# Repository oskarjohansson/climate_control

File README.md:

# Boot Climate Control
> Created by Benjamin Lundgren & Oskar Johansson

Based on [Ski boots hearing system](https://hackaday.io/project/163132-ski-boots-heating-system). 

## Goals 
> The goal of the Boot Climate Control (BCC)
```
- Never ever freeze in the boots
- Warm for ~8h
```

## Directories 
```
climate_control
├── document        # Generic document folder
│   ├── datasheet   # Datasheet for hardware components  
├── hardware        
│   ├── cad         # 3D models
│   │   └── stl     # 3D print files
│   ├── pcb         # Schematic, layout and production files
│   │   └── gerber  # Production files
│   │   └── library # Library for project
├── img             
└── software        # Firmware files
```

## Usage
> Description about how to use the BCC 

## License
> This template is created with MIT license.
>
> ](http://badges.mit-license.org)

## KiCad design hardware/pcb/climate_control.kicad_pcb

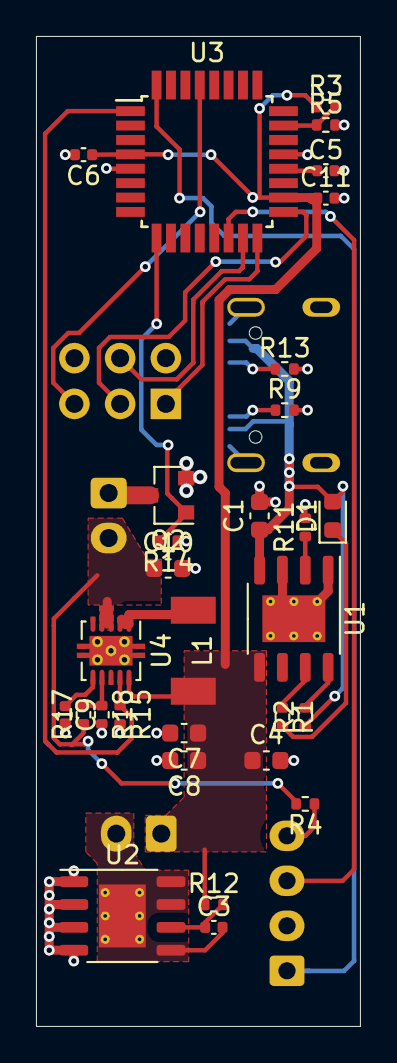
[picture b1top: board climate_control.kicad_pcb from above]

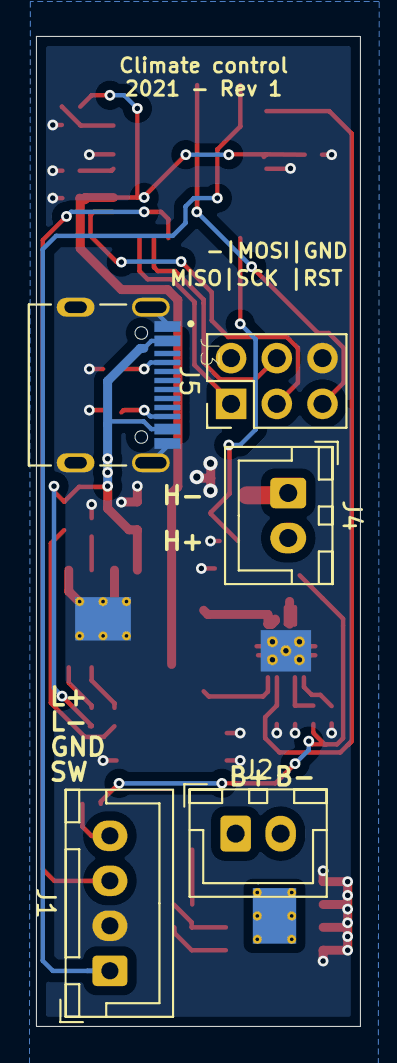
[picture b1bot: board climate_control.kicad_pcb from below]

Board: 2 copper layers, 18.0 x 55.0 mm, 35 parts (5 on the bottom side), 27 nets.

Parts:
C1, C4, C7, C8, C10: 10uF; C_0603_1608Metric
C3, C6, C11: 100nF; C_0402_1005Metric
C5: 1uF; C_0402_1005Metric
C9: 18nF; C_0402_1005Metric
D1: CHRG; D_0603_1608Metric
J1: Switch; JST_XH_B4B-XH-A_1x04_P2.50mm_Vertical
J2: BatteryIn; JST_XH_B2B-XH-A_1x02_P2.50mm_Vertical
J3: USB_C; HRO_TYPE-C-31-M-12
J4: HeatElement; JST_XH_B2B-XH-A_1x02_P2.50mm_Vertical
J5: ICSP; PinHeader_2x03_P2.54mm_Vertical
L1: 1uH; Inductor_0530
Q2: NTR3C21NZ; SOT-23
R1, R4: x; R_0402_1005Metric
R2, R14: 10k; R_0402_1005Metric
R3, R15: 100k; R_0402_1005Metric
R5: 30k; R_0402_1005Metric
R9, R13: 5.1k; R_0402_1005Metric
R11: 2.4k; R_0402_1005Metric
R12: 100R; R_0402_1005Metric
R17, R18: R_Small; R_0402_1005Metric
U1: TP4056; SOP8-EPAD
U2: XB8089A; SOP8-EPAD
U3: ATmega328PB-AU; TQFP-32_7x7mm_P0.8mm
U4: TPS61230DRC; Texas_S-PVSON-N10_ThermalVias

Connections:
+5V: C1.1, D1.2, J3.A4B9, J3.B4A9, R2.1, U1.4
+BATT: C4.1, C6.1, C7.1, C8.1, C11.1, J2.1, L1.1, R3.1, R12.1, U1.5, U3.4, U3.18, U4.10
+VSW: C10.1, J4.2, R4.2, R17.1, U4.3, U4.4
-BATT: C3.2, J2.2, U2.5, U2.7, U2.8, U2.9
BAT: R3.2, R5.1, U3.23
BOOST_EN: R15.1, U3.1, U4.9
GND: C1.2, C4.2, C5.2, C6.2, C7.2, C8.2, C9.2, C10.2, C11.2, J1.2, J3.A1B12, J3.B1A12, J3.S1, J5.6, Q2.2, R5.2, R9.2, R11.2, R13.2, R14.1, R15.2, R18.2, U1.1, U1.3, U1.9, U2.1, U2.2, U2.3, U2.4, U3.5, U3.21, U4.11
HEATER_PWM: Q2.1, R14.2, U3.9
LED: J1.3, U3.14
MISO: J5.1, U3.16
MOSI: J5.4, U3.15
unnamed: C3.1, R12.2, U2.6
unnamed: C5.1, U3.20
unnamed: C9.1, U4.6
unnamed: D1.1, R1.2
unnamed: J1.4, R4.1
unnamed: J3.A5, R13.1
unnamed: J3.B5, R9.1
unnamed: J4.1, Q2.3
unnamed: L1.2, U4.1, U4.2
unnamed: R1.1, U1.7
unnamed: R2.2, U1.8
unnamed: R11.1, U1.2
unnamed: R17.2, R18.1, U4.7
SCK: J5.3, U3.17
SWITCH: J1.1, U3.32
~RST: J5.5, U3.29

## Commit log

2021-02-16 Added components to schematic and library
    Added Battery protection
    Added Boost charger
    Added USB Connector
    Added Boost module
2021-02-16 Added link to hackaday post
2021-02-16 Correct title on battery charger.
    Wrote boost before, when it is a buck charger. Now corrected.
2021-02-17 Added image of Arduino Pro Mini
2021-02-17 Added datasheet for BMS
2021-02-17 Added MCU and better control.
    MCU with all connection is added.
    Output to heater now has a mosfet to PWM to.
    LED Switch has a connection with mosfet to control LED.
    LED Switch has a LP filter for debounce purpose.
2021-02-18 All components added to schematic and pcb.
    Footprints for all parts is done and only routing is left.
2021-02-18 Removed resistor on TP4056.
    Updated on PCB the routing.
2021-02-18 First routing complete.
    The first routing is done, now it must be improved!
2021-02-18 Added comments on LED/Switch circuitry
2021-02-20 Removed unnececary components
2021-02-20 Second routing process done
2021-02-20 Routing complete and added some silkscreen.
2021-02-22 Added datasheet for all components.
    Added datasheet for all components except passives and connectors.
2021-02-22 Added battery divider to MCU.
    A voltage divider from the battery is now connected to the MCU.
    The divider is designed to work with the internal voltage reference (1V1).
    With the resistor values, a battery voltage of 5 V will be 1.15 at MCU.
2021-02-23 Removed crystal.
    The ATMega does not need an external crystal. Now removed.
2021-02-23 Export .stp from PCB.
2021-02-25 Final first revision ordered.
2021-03-11 More preparations in code. (SOC)
2021-03-11 Createt Platform-IO project + structured files
2021-03-16 Changed platformIo settings
    Upload settings for using atmel ice in ubuntu.
    Board frequency and fuses to get correct timing.
2021-03-16 Software verification
    Tested
    - enabling of boost converter
    - toggling led
    - reading button
    - debouncing and click pattern detection
2021-04-12 Fixed sleep and changing power level. Still too high sleep current.
2021-04-13 Fixed sleeping issue and led indication for heater
2021-04-14 Added SOC led blinks.
    The LED will now blink according to the return of getSoc.
    There are three levels,
    0% - 40%, 40% - 70% and 70% - 100%.
    One blink is lowest and three is full.
2021-04-15 Show SOC
2021-04-21 Added fuse settings for ATMega328PB
2021-04-21 Fixed deadlock when sleeping (Hopefully :) )
2023-12-31 Convert to Kicad 7
